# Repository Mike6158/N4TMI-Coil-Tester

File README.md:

# N4TMI-Coil-Tester
N4TMI Coil Test Oscillator
This circut was originally published in 73 magazine by N4TMI. 
It has since been republished at: https://www.radio-collector.com/coil-resonance-tester/
W2AEW's YouTube Channel has a nice video about how to determine the value of the device under test.
You can find it here: https://youtu.be/Ff5xOENID7w
I've built the circuit, modified to W2AEW's version, and it works. The board file is on Osh Park and 
can be found here: <a href="https://oshpark.com/shared_projects/gx7Ixj44"></img></a>
Or you can use or modify the included Eagle files as you wish

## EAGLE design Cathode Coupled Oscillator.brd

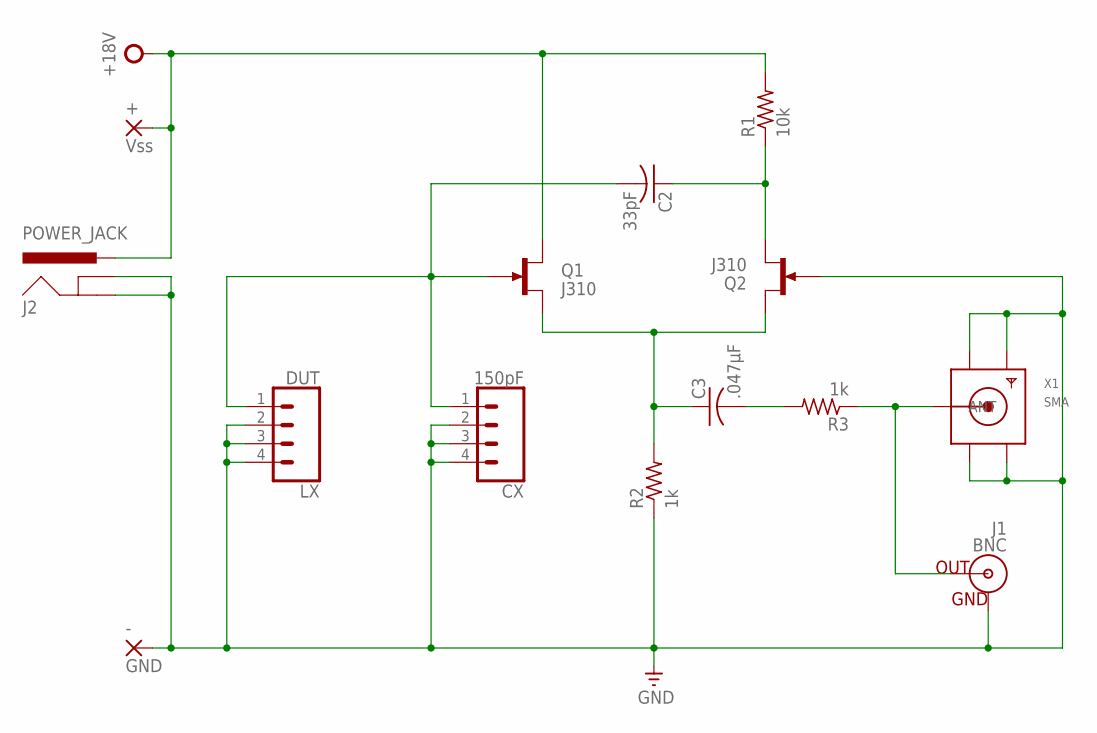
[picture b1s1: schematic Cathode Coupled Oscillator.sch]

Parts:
+: Vss; 2,54/1,0
-: GND; 2,54/1,0
C2: 33pF; C0805
C3: .047µF; C0805
CX: 150pF; 1X04
J1: BNC
J2: POWER_JACK; POWER_JACK_PTH
LX: DUT; 1X04
Q1, Q2: J310; SOT23
R1: 10k; R0805
R2, R3: 1k; R0805
X1: SMA; SMA90_DIP

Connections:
+18V: +.1, J2.PWR, Q1.1 (D), R1.2
GND: -.1, CX.2, CX.3, CX.4, J1.GND, J2.GND, J2.GNDBREAK, LX.2, LX.3, LX.4, Q2.3 (G), R2.1, X1.GND1, X1.GND2, X1.GND3, X1.GND4
unnamed: C2.1, Q2.2 (S), R1.1
unnamed: C2.2, CX.1, LX.1, Q1.3 (G)
unnamed: J1.S (OUT), R3.1, X1.ANTENNA (ANT)
unnamed: C3.2, R3.2
unnamed: C3.1, Q1.2 (S), Q2.1 (D), R2.2

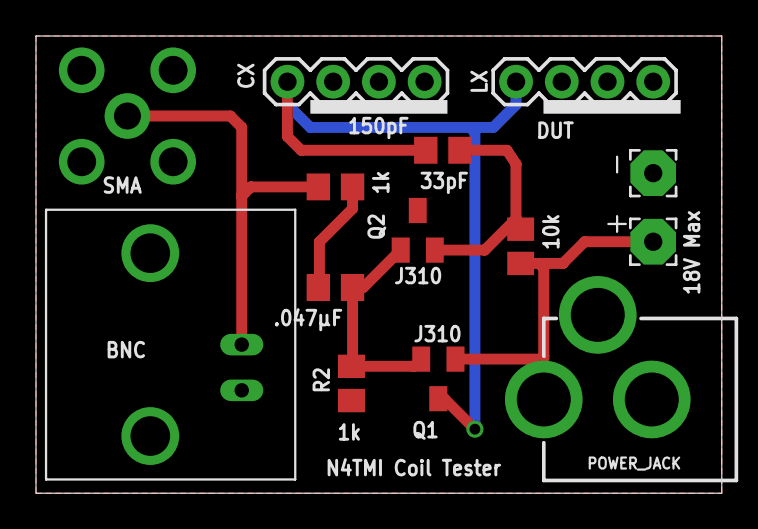
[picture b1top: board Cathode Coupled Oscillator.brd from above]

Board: 2 copper layers, 38.1 x 25.4 mm, 14 parts (0 on the bottom side), 7 nets.

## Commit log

2018-01-01 N4TMI Coil Tester Readme

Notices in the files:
parts and their libraries:
SparkFun-Connectors: Licensing: Creative Commons ShareAlike 4.0 International - https://creativecommons.org/licenses/by-sa/4.0
